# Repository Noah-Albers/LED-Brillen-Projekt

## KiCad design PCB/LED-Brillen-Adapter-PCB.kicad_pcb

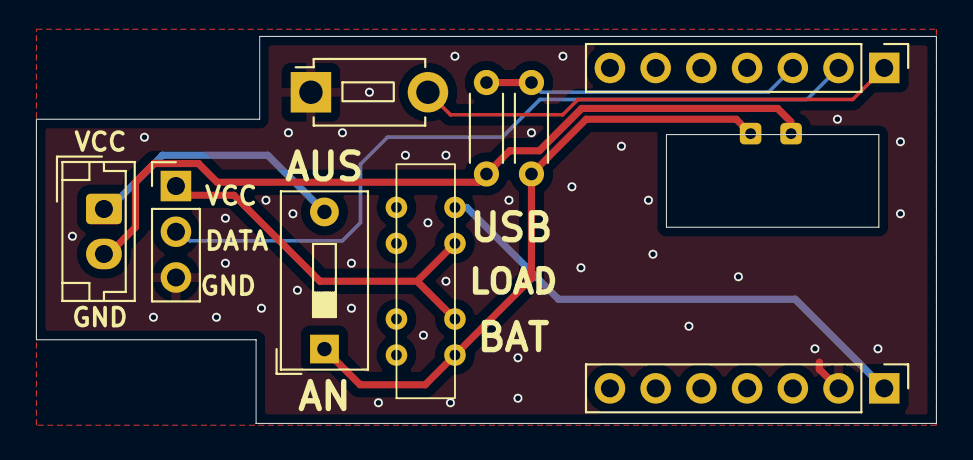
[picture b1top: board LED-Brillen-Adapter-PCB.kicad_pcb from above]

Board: 2 copper layers, 50.0 x 21.5 mm, 10 parts (0 on the bottom side), 9 nets.

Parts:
J1, J2: Conn_01x07_Pin; PinHeader_1x07_P2.54mm_Vertical
J3: Conn_01x03_Pin; PinHeader_1x03_P2.54mm_Vertical
J4: Conn_01x02; Battery-Adapter
J5: Conn_01x02; JST_EH_B2B-EH-A_1x02_P2.50mm_Vertical
R1, R2: R; R_Axial_DIN0204_L3.6mm_D1.6mm_P5.08mm_Horizontal
SW1: SW_DIP_x01; SW_DIP_SPSTx01_Slide_9.78x4.72mm_W7.62mm_P2.54mm
SW2: SW_Push; SW_PUSH_1P1T_6x3.5mm_H5.0_APEM_MJTP1250
SW3: MSS-2336

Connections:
3,7V (BAT): J4.1, R2.2, SW1.1, SW3.1
5V (USB): J1.1, SW3.4
/BTN: J2.1, SW2.2
/Battery-Measurement: J2.3, R1.2, R2.1
/LEDS: J2.2, J3.2
GND (Battery): J4.2, J5.2, R1.1
GND (ESP): J1.2, J3.3, SW2.1
unnamed: J5.1, SW1.2
VCC (Stripe): J3.1, SW3.2, SW3.3

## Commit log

2024-05-06 Dumped first version
2024-05-09 Create subdirectory for the pcb
2024-05-09 3d Model der PCB hinzugefügt. Infos bzgl. der Batterie hinzugefügt
2024-06-21 Added rev. 3
2024-06-21 Removed Gehäuse, added Materialliste
2024-07-18 Notizen hinzugefügt. Sollen genutzt werden um Zeugs für später zu merken
2024-07-18 Erste rev. des Batterie-Case hinzugefügt
2024-07-23 Added rev 2 Batterie casing
2024-07-23 Rev. 3 Batterie-Case hinzugefügt
2024-07-23 Rev. 4 Batteriecasing hinzugefügt
